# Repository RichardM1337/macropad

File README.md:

# MacroPad-for-Productivity
A MacroPad that will help enhance my workflow and productivity in writing documents.

This project was my introduction into hardware design with PCB. I would say this was pretty hard but after learning it I was able to become way more knowledgeable. I enjoyed this project a lot!

# 3D CAD Model
The case was built through AutoDesk Inventor, and I imported the 3D model of the pcb + components for a 3D view of the actual macropad.

# PCB
KiCAD was used from schematics to the actual PCB design.

- Schematic
- 
- PCB with zones
- 

# Firmware
I used QMK for the macropad's firmware. I made the 5 keys have productivity enhancement commands such as copy and paste. The rotary encoder will be used for volume control.

# BOM (Bill of Materials)
|Quantity|Material|Unit Price|Total Price|Link|
|---|---|---|---|---|
|1|Seeed XIAO RP2040|$4.10|$4.10|https://www.seeedstudio.com/XIAO-RP2040-v1-0-p-5026.html?srsltid=AfmBOoqOA5pbs0-SnX0Snq-TFv7ZKOE11QVVoSF44PknPpL5-1QgLOM1|
|1|EC11 Rotary Encoder|$2.10|$2.10|https://keeb.io/products/rotary-encoder-ec11?srsltid=AfmBOorymYf9p4A50xB9ApIyCCR5Cf_eKUdUsuJ3HonTKL7SfaL5IICn|
|4|M3x16mm Screws|$1.41|$1.96 (Discount for ordering 1+)|https://accu-components.com/us/metric-cap-head-screws/3822-SSCF-M3-16-A2?srsltid=AfmBOop6K_4plw_Z9O1RUv1B5p-NnPDPHdZk4CypNsCyyPLQcBvUpQZs|
|5|MX-Style Switches|$0.40|$2.08|https://mechanicalkeyboards.com/products/cherry-mx-blue-60g-clicky?variant=48007305003308&country=US&currency=USD&utm_medium=product_sync&utm_source=google&utm_content=sag_organic&utm_campaign=sag_organic&srsltid=AfmBOooLWB1cQSYnyB0cPi6i3iMJLBsXu-NKrlc5z8O5IFLtwBtzYG9nT6s|
|5|White Blank DSA Keycaps|$5.95|$5.95 (10 pack)|https://www.adafruit.com/product/4998?srsltid=AfmBOorCD8XMgbDWvV6vtG266_8ozohsP-0gxKIEfWXDAyuclgszwk92|
|1|PCB Estimated Price|$2.15|$2.15|

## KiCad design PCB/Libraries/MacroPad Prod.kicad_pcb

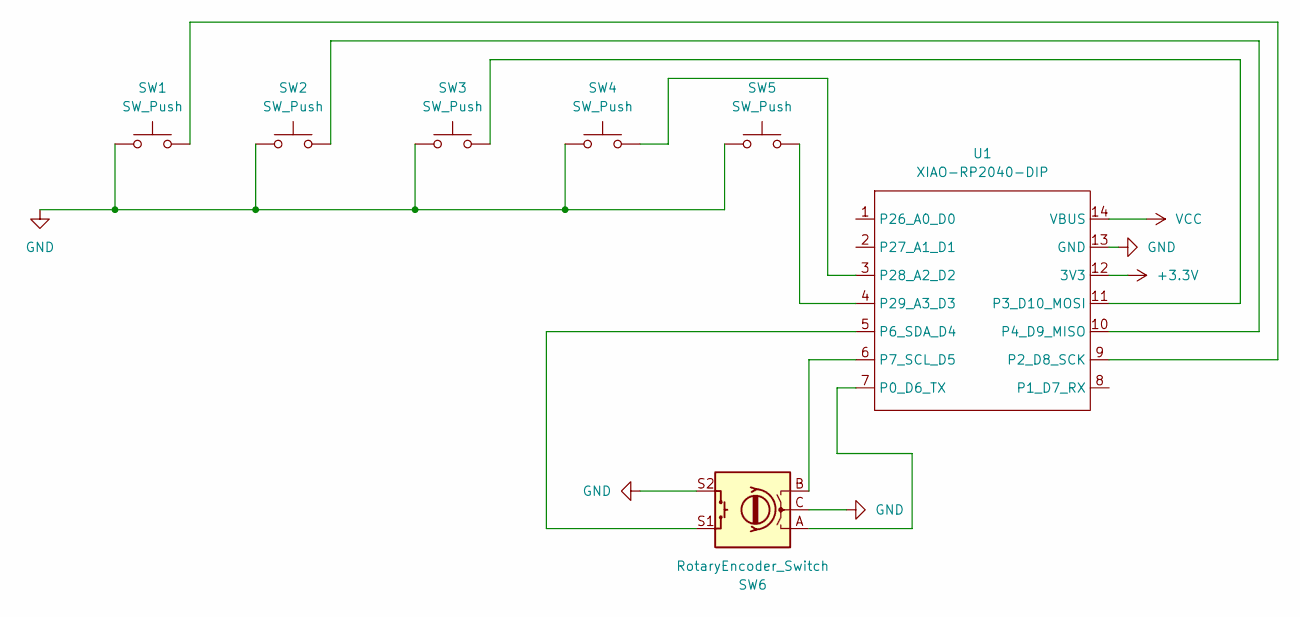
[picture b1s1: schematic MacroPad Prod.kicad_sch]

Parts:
SW1, SW2, SW3, SW4, SW5: SW_Push; SW_Cherry_MX_1.00u_PCB
SW6: RotaryEncoder_Switch; RotaryEncoder_Alps_EC11E-Switch_Vertical_H20mm
U1: XIAO-RP2040-DIP

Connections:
+3.3V: U1.12 (3V3)
GND: SW1.1, SW2.1, SW3.1, SW4.1, SW5.1, SW6.C, SW6.S2, U1.13 (GND)
unnamed: SW6.A, U1.7 (P0_D6_TX)
unnamed: SW1.2, U1.9 (P2_D8_SCK)
unnamed: SW3.2, U1.11 (P3_D10_MOSI)
unnamed: SW2.2, U1.10 (P4_D9_MISO)
unnamed: SW6.S1, U1.5 (P6_SDA_D4)
unnamed: SW6.B, U1.6 (P7_SCL_D5)
unnamed: SW4.2, U1.3 (P28_A2_D2)
unnamed: SW5.2, U1.4 (P29_A3_D3)
VCC: U1.14 (VBUS)

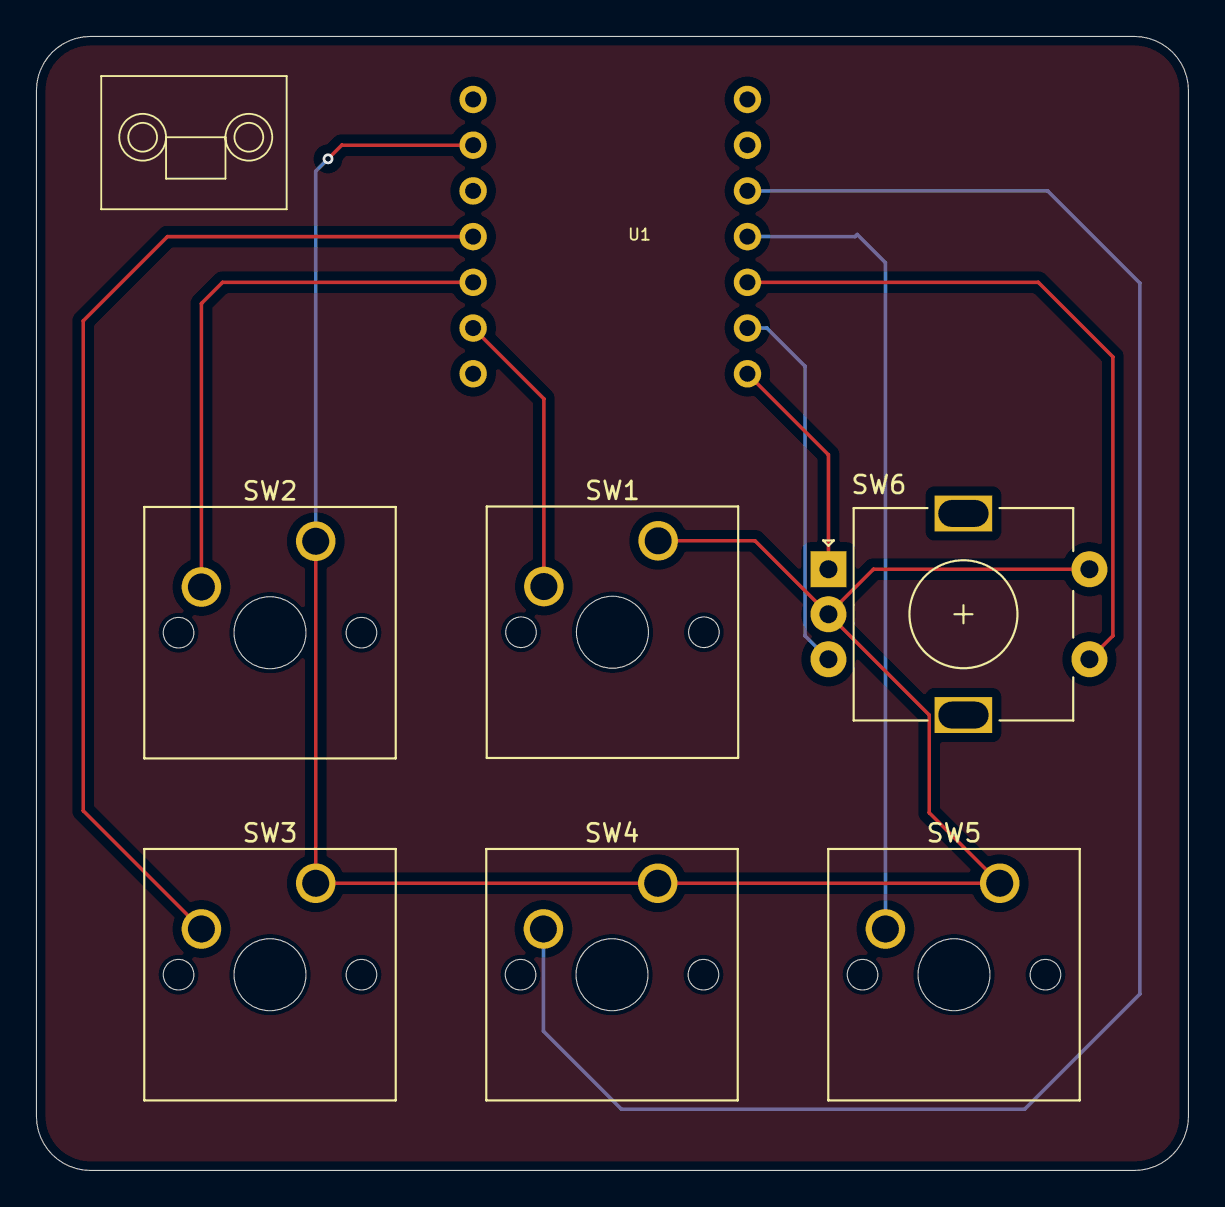
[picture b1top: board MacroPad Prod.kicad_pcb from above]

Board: 2 copper layers, 64.0 x 63.0 mm, 7 parts (1 on the bottom side), 9 nets.

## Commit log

2026-05-04 Update image links in README.md to raw GitHub URLs
